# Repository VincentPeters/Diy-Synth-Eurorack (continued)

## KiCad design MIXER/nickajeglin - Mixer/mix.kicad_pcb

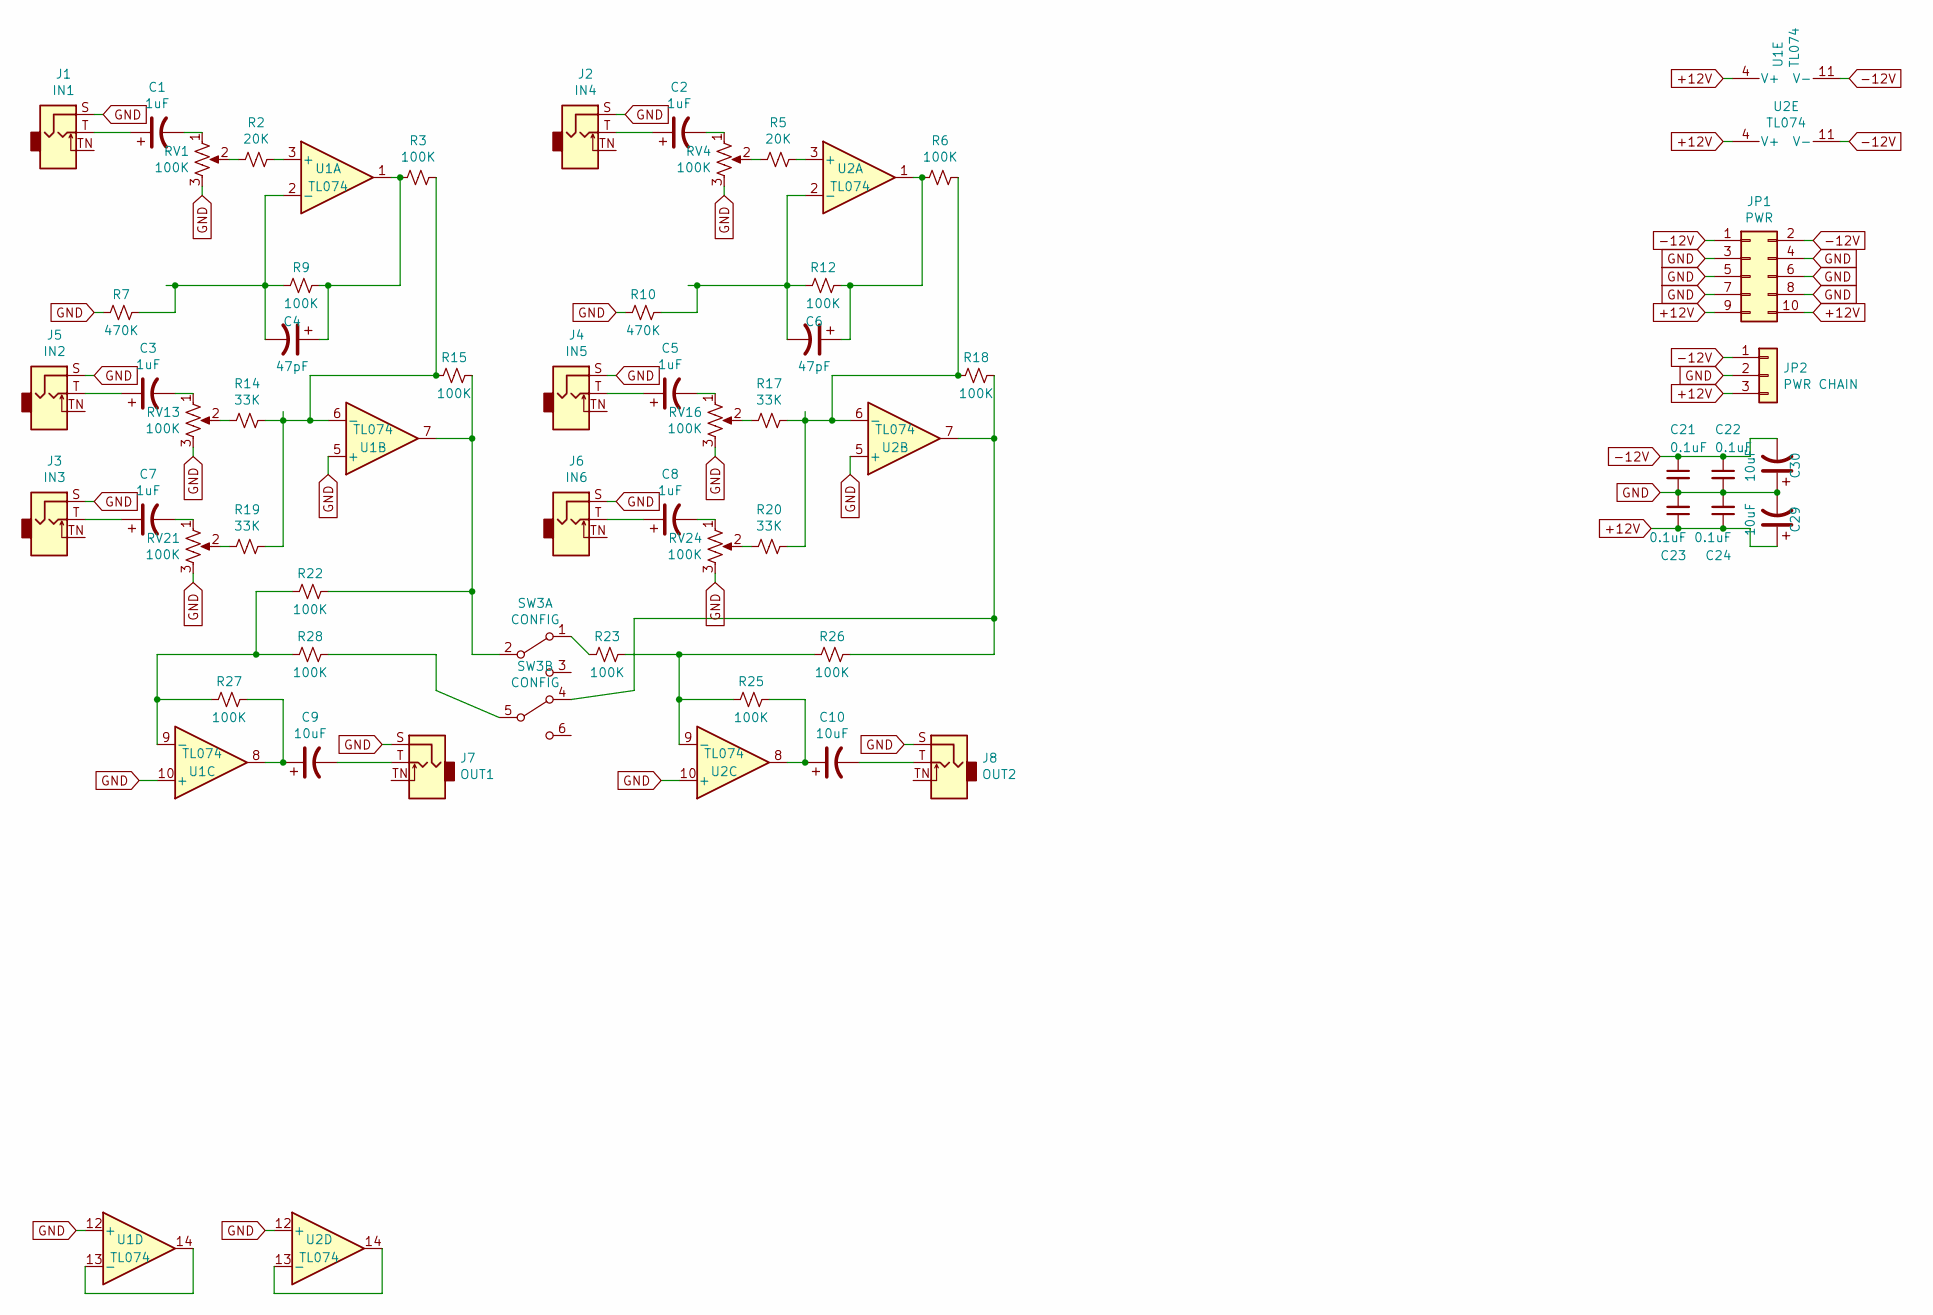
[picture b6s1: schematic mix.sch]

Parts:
C1, C2, C3, C5, C7, C8: 1uF; CP_Elec_6.3x5.4
C4, C6: 47pF; C_1206_3216Metric_Pad1.42x1.75mm_HandSolder
C9, C10, C29, C30: 10uF; CP_Elec_6.3x5.4
C21, C22, C23, C24: 0.1uF; C_1206_3216Metric_Pad1.42x1.75mm_HandSolder
J1: IN1; 3.5mm_tip_switch_thonkiconn
J2: IN4; 3.5mm_tip_switch_thonkiconn
J3: IN3; 3.5mm_tip_switch_thonkiconn
J4: IN5; 3.5mm_tip_switch_thonkiconn
J5: IN2; 3.5mm_tip_switch_thonkiconn
J6: IN6; 3.5mm_tip_switch_thonkiconn
J7: OUT1; 3.5mm_tip_switch_thonkiconn
J8: OUT2; 3.5mm_tip_switch_thonkiconn
JP1: PWR; IDC-Header_2x05_P2.54mm_Vertical
JP2: PWR CHAIN; PinHeader_1x03_P2.54mm_Vertical
R2, R5: 20K; R_1206_3216Metric_Pad1.42x1.75mm_HandSolder
R3, R6, R9, R12, R15, R18, R22, R23, R25, R26, R27, R28: 100K; R_1206_3216Metric_Pad1.42x1.75mm_HandSolder
R7, R10: 470K; R_1206_3216Metric_Pad1.42x1.75mm_HandSolder
R14, R17, R19, R20: 33K; R_1206_3216Metric_Pad1.42x1.75mm_HandSolder
RV1, RV4, RV13, RV16, RV21, RV24: 100K; Potentiometer_Thonk_Alpha_9mm_Vertical
SW3: CONFIG; toggle_switch_mini_DPDT
U1, U2: TL074; SOIC-14_3.9x8.7mm_P1.27mm

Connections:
+12V: C23.1, C24.1, C29.1, JP1.9, JP1.10, JP2.3, U1.4 (V+), U2.4 (V+)
-12V: C21.1, C22.1, C30.2, JP1.1, JP1.2, JP2.1, U1.11 (V-), U2.11 (V-)
GND: C21.2, C22.2, C23.2, C24.2, C29.2, C30.1, J1.S, J2.S, J3.S, J4.S, J5.S, J6.S, J7.S, J8.S, JP1.3, JP1.4, JP1.5, JP1.6, JP1.7, JP1.8, JP2.2, R7.2, R10.2, RV1.3, RV4.3, RV13.3, RV16.3, RV21.3, RV24.3, U1.5 (+), U1.10 (+), U1.12 (+), U2.5 (+), U2.10 (+), U2.12 (+)
unnamed: C1.1, J1.T
unnamed: C1.2, RV1.1
unnamed: C2.1, J2.T
unnamed: C2.2, RV4.1
unnamed: C3.1, J5.T
unnamed: C3.2, RV13.1
unnamed: C4.1, R3.2, R9.1, U1.1
unnamed: C5.1, J4.T
unnamed: C5.2, RV16.1
unnamed: C6.1, R6.2, R12.1, U2.1
unnamed: C7.1, J3.T
unnamed: C7.2, RV21.1
unnamed: C8.1, J6.T
unnamed: C8.2, RV24.1
unnamed: C9.1, R27.1, U1.8
unnamed: C9.2, J7.T
unnamed: C10.1, R25.1, U2.8
unnamed: C10.2, J8.T
unnamed: R2.1, U1.3 (+)
unnamed: R2.2, RV1.2
unnamed: R5.1, U2.3 (+)
unnamed: R5.2, RV4.2
unnamed: R3.1, R14.1, R15.2, R19.1, U1.6 (-)
unnamed: R14.2, RV13.2
unnamed: R15.1, R22.1, SW3.2 (B), U1.7
unnamed: R6.1, R17.1, R18.2, R20.1, U2.6 (-)
unnamed: R17.2, RV16.2
unnamed: R18.1, R26.1, SW3.4 (A), U2.7
unnamed: R19.2, RV21.2
unnamed: R20.2, RV24.2
unnamed: R22.2, R27.2, R28.2, U1.9 (-)
unnamed: R23.1, R25.2, R26.2, U2.9 (-)
unnamed: R23.2, SW3.1 (A)
unnamed: R28.1, SW3.5 (B)
unnamed: U1.13 (-), U1.14
unnamed: U2.13 (-), U2.14

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
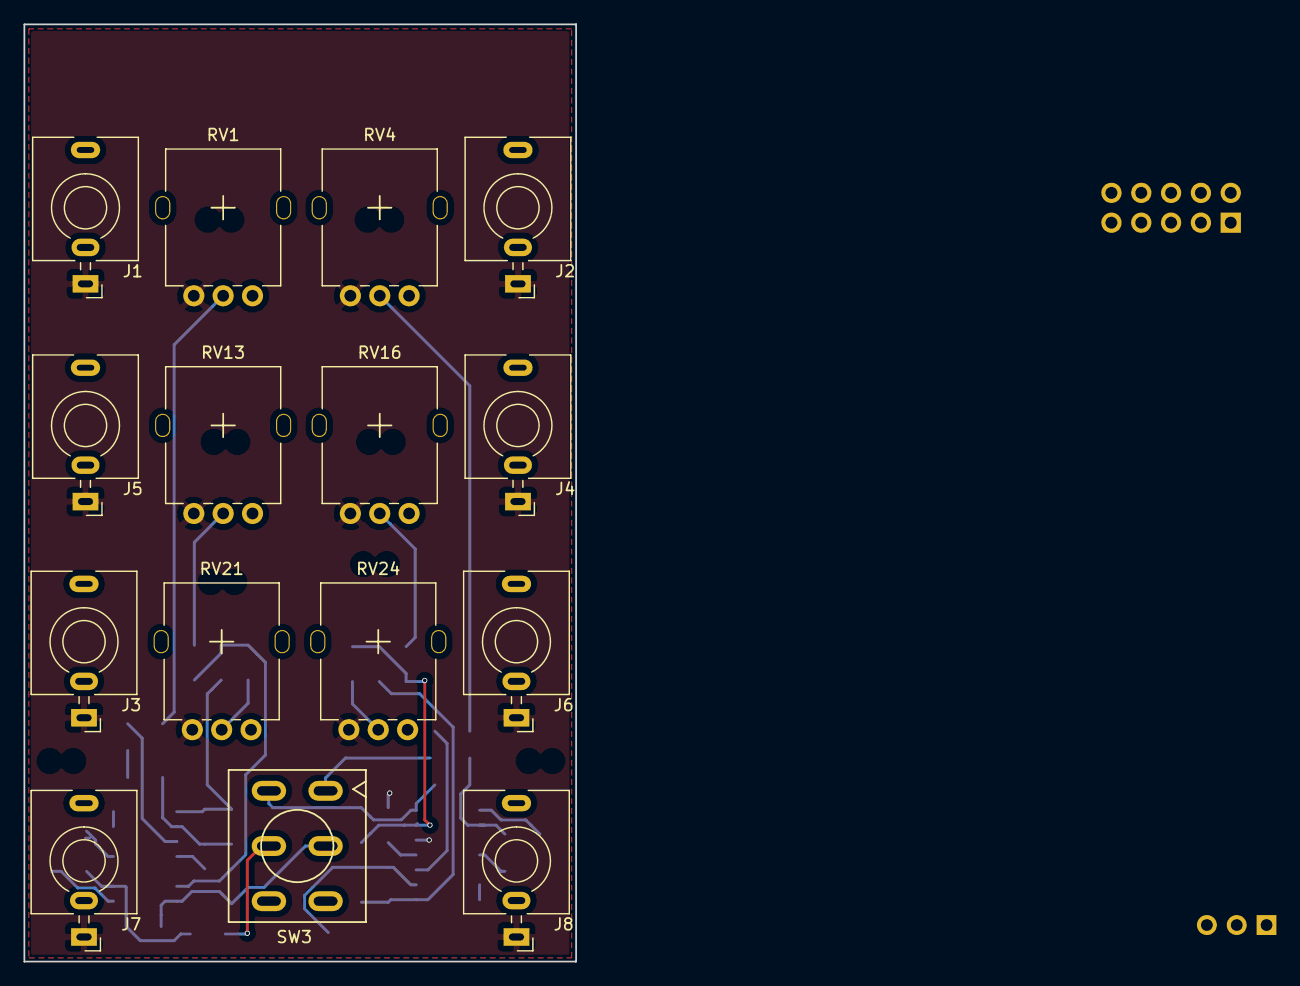
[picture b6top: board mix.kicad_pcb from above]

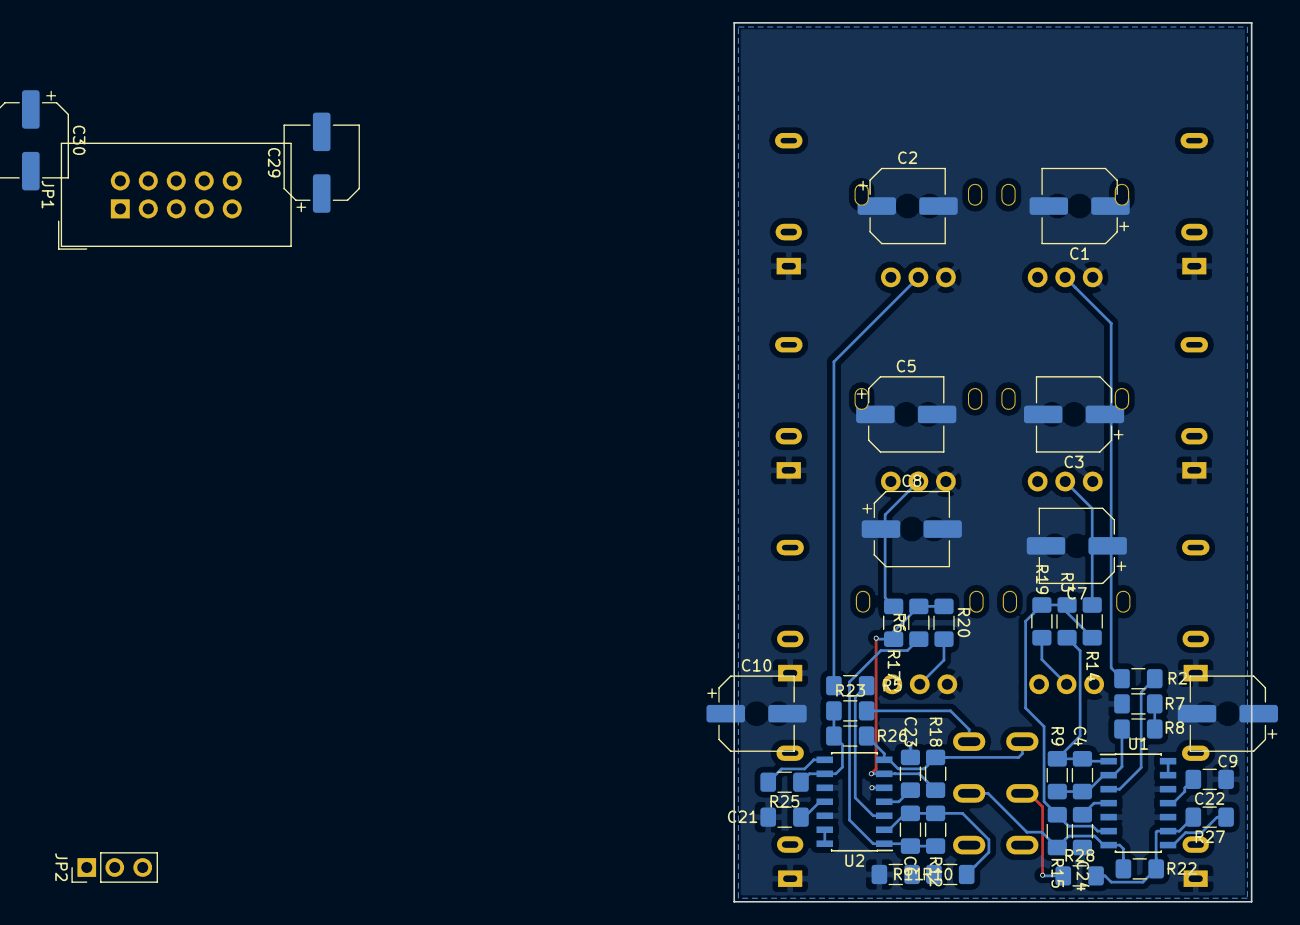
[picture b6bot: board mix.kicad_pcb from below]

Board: 2 copper layers, 47.0 x 79.8 mm, 57 parts (42 on the bottom side), 43 nets.

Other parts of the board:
R8, R11: 2K; R_1206_3216Metric_Pad1.42x1.75mm_HandSolder

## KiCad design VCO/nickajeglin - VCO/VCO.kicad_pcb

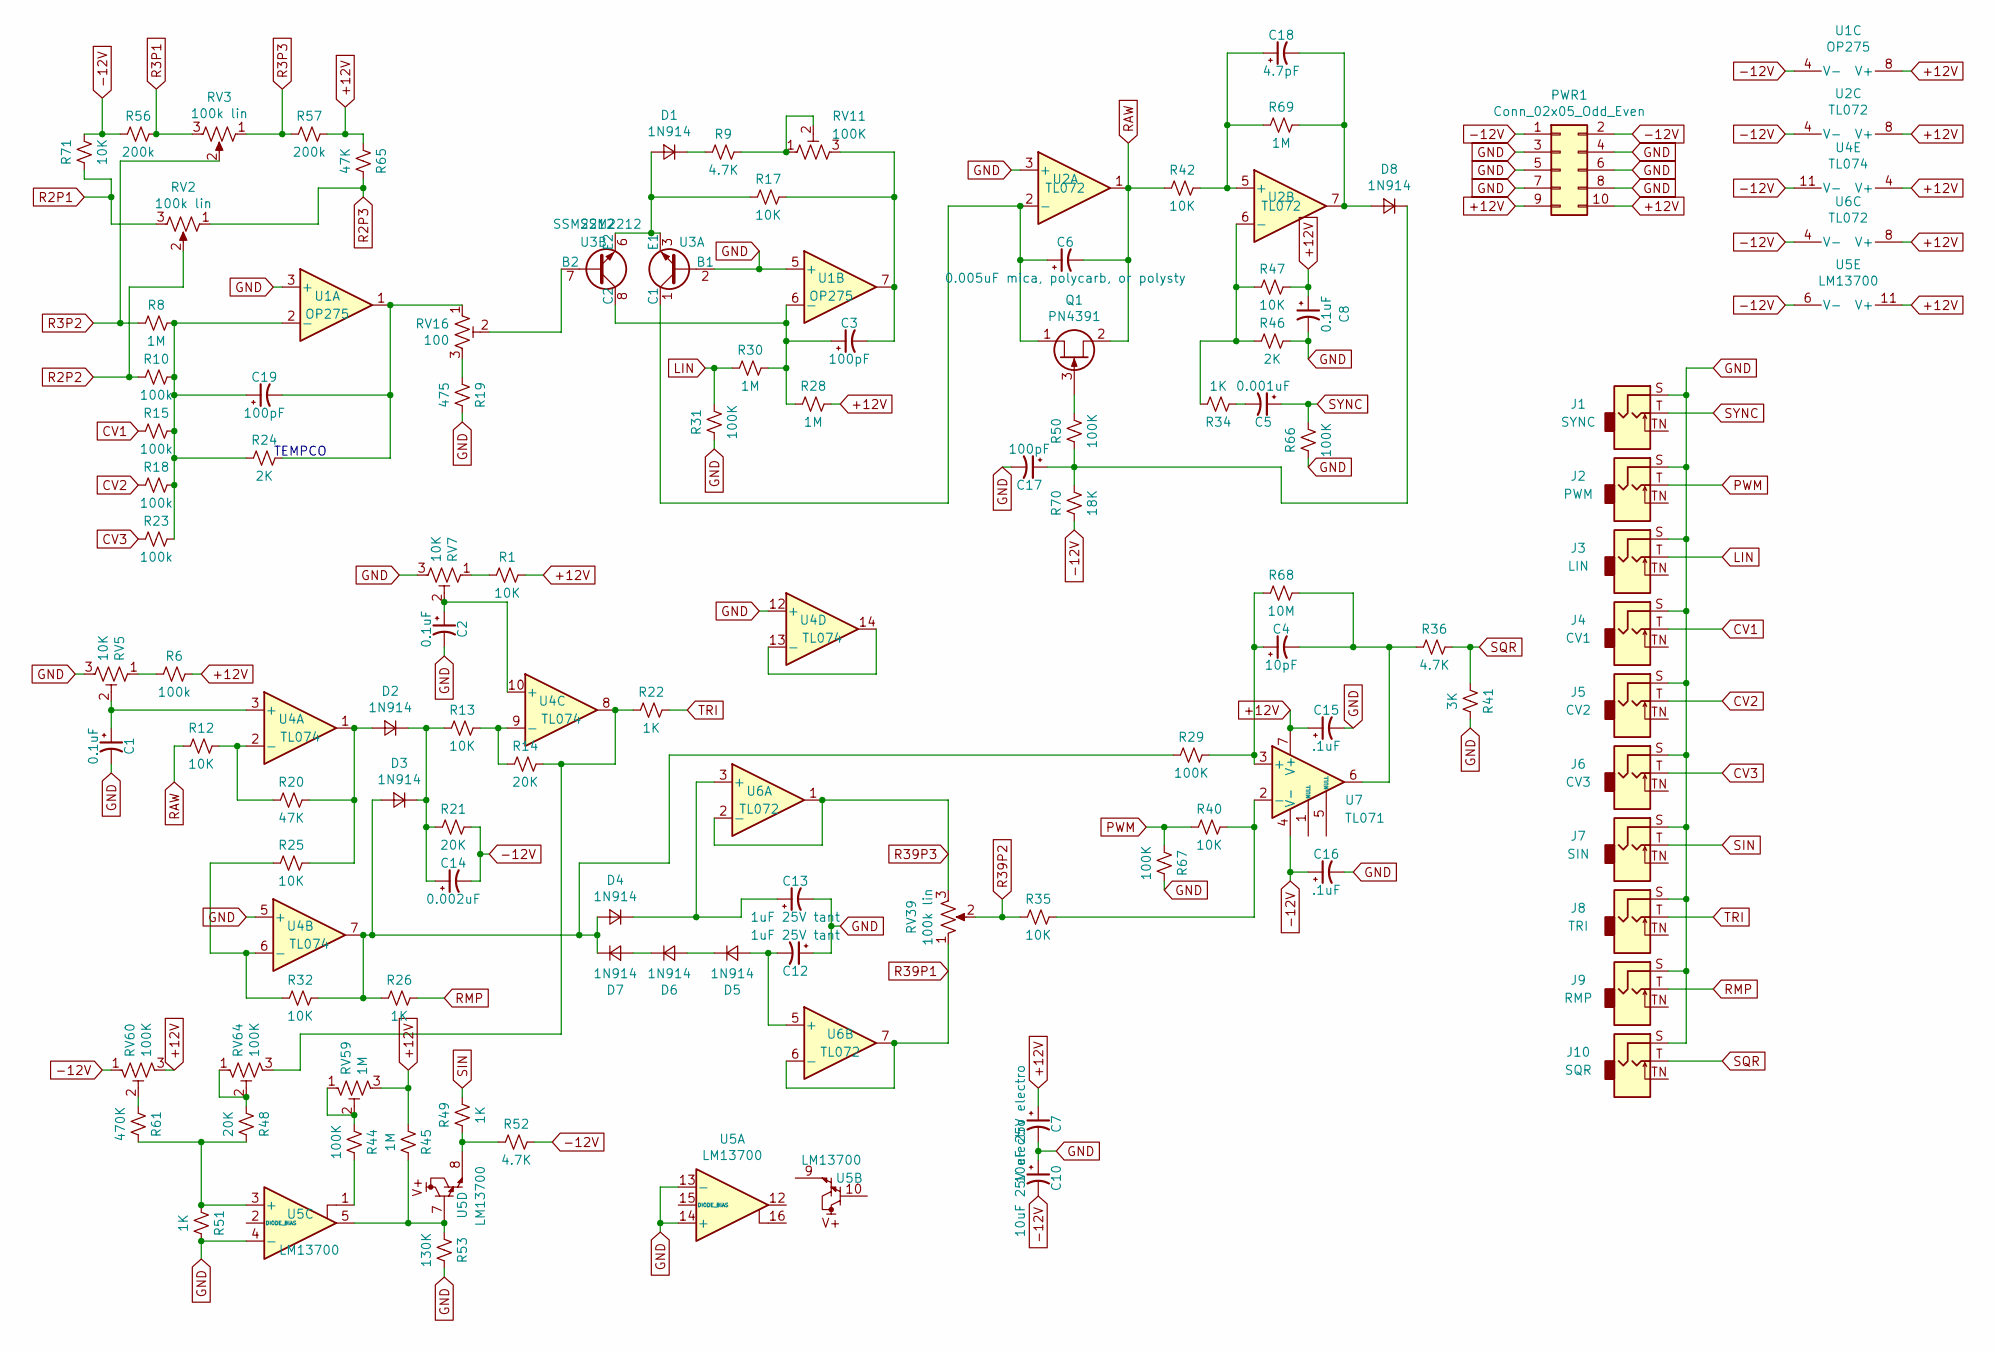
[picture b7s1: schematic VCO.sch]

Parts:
C1, C2, C8: 0.1uF; C_1206_3216Metric_Pad1.42x1.75mm_HandSolder
C3, C17, C19: 100pF; C_1206_3216Metric_Pad1.42x1.75mm_HandSolder
C4: 10pF; C_1206_3216Metric_Pad1.42x1.75mm_HandSolder
C5: 0.001uF; C_1206_3216Metric_Pad1.42x1.75mm_HandSolder
C6: 0.005uF mica, polycarb, or polysty; C_1206_3216Metric_Pad1.42x1.75mm_HandSolder
C7, C10: 10uF 25V electro; CP_Radial_D5.0mm_P2.50mm
C12, C13: 1uF 25V tant; C_1206_3216Metric_Pad1.42x1.75mm_HandSolder
C14: 0.002uF; C_1206_3216Metric_Pad1.42x1.75mm_HandSolder
C15, C16: .1uF; C_1206_3216Metric_Pad1.42x1.75mm_HandSolder
C18: 4.7pF; C_1206_3216Metric_Pad1.42x1.75mm_HandSolder
D1, D2, D3, D4, D5, D6, D7, D8: 1N914; D_1206_3216Metric_Pad1.42x1.75mm_HandSolder
J1: SYNC; 3.5mm_tip_switch_thonkiconn
J2: PWM; 3.5mm_tip_switch_thonkiconn
J3: LIN; 3.5mm_tip_switch_thonkiconn
J4: CV1; 3.5mm_tip_switch_thonkiconn
J5: CV2; 3.5mm_tip_switch_thonkiconn
J6: CV3; 3.5mm_tip_switch_thonkiconn
J7: SIN; 3.5mm_tip_switch_thonkiconn
J8: TRI; 3.5mm_tip_switch_thonkiconn
J9: RMP; 3.5mm_tip_switch_thonkiconn
J10: SQR; 3.5mm_tip_switch_thonkiconn
PWR1: Conn_02x05_Odd_Even; IDC-Header_2x05_P2.54mm_Vertical
Q1: PN4391; TO-92_Inline
R1, R12, R13, R17, R25, R32, R35, R40, R42, R47, R71: 10K; R_1206_3216Metric_Pad1.42x1.75mm_HandSolder
R6, R10, R15, R18, R23: 100k; R_1206_3216Metric_Pad1.42x1.75mm_HandSolder
R8, R28, R30, R45, R69: 1M; R_1206_3216Metric_Pad1.42x1.75mm_HandSolder
R9, R36, R52: 4.7K; R_1206_3216Metric_Pad1.42x1.75mm_HandSolder
R14, R21, R48: 20K; R_1206_3216Metric_Pad1.42x1.75mm_HandSolder
R19: 475; R_1206_3216Metric_Pad1.42x1.75mm_HandSolder
R20, R65: 47K; R_1206_3216Metric_Pad1.42x1.75mm_HandSolder
R22, R26, R34, R49, R51: 1K; R_1206_3216Metric_Pad1.42x1.75mm_HandSolder
R24, R46: 2K; R_1206_3216Metric_Pad1.42x1.75mm_HandSolder
R29, R31, R44, R50, R66, R67: 100K; R_1206_3216Metric_Pad1.42x1.75mm_HandSolder
R41: 3K; R_1206_3216Metric_Pad1.42x1.75mm_HandSolder
R53: 130K; R_1206_3216Metric_Pad1.42x1.75mm_HandSolder
R56, R57: 200k; R_1206_3216Metric_Pad1.42x1.75mm_HandSolder
R61: 470K; R_1206_3216Metric_Pad1.42x1.75mm_HandSolder
R68: 10M; R_1206_3216Metric_Pad1.42x1.75mm_HandSolder
R70: 18K; R_1206_3216Metric_Pad1.42x1.75mm_HandSolder
RV2, RV3, RV39: 100k lin; Potentiometer_Alps_RK09K_Single_Vertical
RV5, RV7: 10K; Potentiometer_Bourns_3296W_Vertical
RV11, RV60, RV64: 100K; Potentiometer_Bourns_3296W_Vertical
RV16: 100; Potentiometer_Bourns_3296W_Vertical
RV59: 1M; Potentiometer_Bourns_3296W_Vertical
U1: OP275; SOIC-8_3.9x4.9mm_P1.27mm
U2, U6: TL072; SOIC-8_3.9x4.9mm_P1.27mm
U3: SSM2212; SOIC-8_3.9x4.9mm_P1.27mm
U4: TL074; SOIC-14_3.9x8.7mm_P1.27mm
U5: LM13700; SOIC-16_3.9x9.9mm_P1.27mm
U7: TL071; SOIC-8_3.9x4.9mm_P1.27mm

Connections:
+12V: C7.1, C8.1, C15.1, PWR1.9, PWR1.10, R1.1, R6.1, R28.1, R45.2, R47.1, R57.1, R65.2, RV59.3, RV60.3, U1.8 (V+), U2.8 (V+), U4.4 (V+), U5.11 (V+), U6.8 (V+), U7.7 (V+)
-12V: C10.2, C14.2, C16.1, PWR1.1, PWR1.2, R21.1, R52.1, R56.2, R70.2, R71.1, RV60.1, U1.4 (V-), U2.4 (V-), U4.11 (V-), U5.6 (V-), U6.4 (V-), U7.4 (V-)
CV1: J4.T, R15.2
CV2: J5.T, R18.2
CV3: J6.T, R23.2
GND: C1.2, C2.2, C7.2, C8.2, C10.1, C12.1, C13.2, C15.2, C16.2, C17.2, J1.S, J2.S, J3.S, J4.S, J5.S, J6.S, J7.S, J8.S, J9.S, J10.S, PWR1.3, PWR1.4, PWR1.5, PWR1.6, PWR1.7, PWR1.8, R19.1, R31.2, R41.1, R46.1, R51.1, R53.1, R66.2, R67.1, RV5.3, RV7.3, U1.3 (+), U1.5 (+), U2.3 (+), U3.2 (B1), U4.5 (+), U4.12 (+), U5.4 (-), U5.13 (-), U5.14 (+)
LIN: J3.T, R30.2, R31.1
unnamed: C1.1, RV5.2, U4.3 (+)
unnamed: C2.1, RV7.2, U4.10 (+)
unnamed: C3.1, R28.2, R30.1, U1.6 (-), U3.8 (C2)
unnamed: C3.2, R17.1, RV11.3, U1.7
unnamed: C4.1, R29.1, R68.2, U7.3 (+)
unnamed: C4.2, R36.2, R68.1, U7.6
unnamed: C5.2, R34.2
unnamed: C6.1, Q1.1 (D), U2.2 (-), U3.1 (C1)
unnamed: C12.2, D5.2 (A), U6.5 (+)
unnamed: C13.1, D4.1 (K), U6.3 (+)
unnamed: C14.1, D2.1 (K), D3.1 (K), R13.2, R21.2
unnamed: C17.1, D8.1 (K), R50.2, R70.1
unnamed: C18.1, R42.1, R69.2, U2.5 (+)
unnamed: C18.2, D8.2 (A), R69.1, U2.7
unnamed: C19.1, R8.1, R10.1, R15.1, R18.1, R23.1, R24.2, U1.2 (-)
unnamed: C19.2, R24.1, RV16.1, U1.1
unnamed: D1.1 (K), R9.2
unnamed: D1.2 (A), R17.2, U3.3 (E1), U3.6 (E2)
unnamed: D2.2 (A), R20.1, R25.1, U4.1
unnamed: D3.2 (A), D4.2 (A), D7.1 (K), R26.2, R29.2, R32.1, U4.7
unnamed: D5.1 (K), D6.2 (A)
unnamed: D6.1 (K), D7.2 (A)
unnamed: Q1.3 (G), R50.1
unnamed: R1.2, RV7.1
unnamed: R6.2, RV5.1
unnamed: R9.1, RV11.1, RV11.2
unnamed: R12.1, R20.2, U4.2 (-)
unnamed: R13.1, R14.2, U4.9 (-)
unnamed: R14.1, R22.2, RV64.3, U4.8
unnamed: R19.2, RV16.3
unnamed: R25.2, R32.2, U4.6 (-)
unnamed: R34.1, R46.2, R47.2, U2.6 (-)
unnamed: R35.1, R40.1, U7.2 (-)
unnamed: R44.1, U5.1
unnamed: R44.2, RV59.1, RV59.2
unnamed: R45.1, R53.2, U5.5, U5.7
unnamed: R48.1, R51.2, R61.1, U5.3 (+)
unnamed: R48.2, RV64.1, RV64.2
unnamed: R49.2, R52.2, U5.8
unnamed: R61.2, RV60.2
unnamed: RV16.2, U3.7 (B2)
unnamed: U4.13 (-), U4.14
PWM: J2.T, R40.2, R67.2
R2P1: R71.2, RV2.3
R2P2: R10.2, RV2.2
R2P3: R65.1, RV2.1
R3P1: R56.1, RV3.3
R3P2: R8.2, RV3.2
R3P3: R57.2, RV3.1
R39P1: RV39.1, U6.6 (-), U6.7
R39P2: R35.2, RV39.2
R39P3: RV39.3, U6.1, U6.2 (-)
RAW: C6.2, Q1.2 (S), R12.2, R42.2, U2.1
RMP: J9.T, R26.1
SIN: J7.T, R49.1
SQR: J10.T, R36.1, R41.2
SYNC: C5.1, J1.T, R66.1
TRI: J8.T, R22.1

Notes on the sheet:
TEMPCO

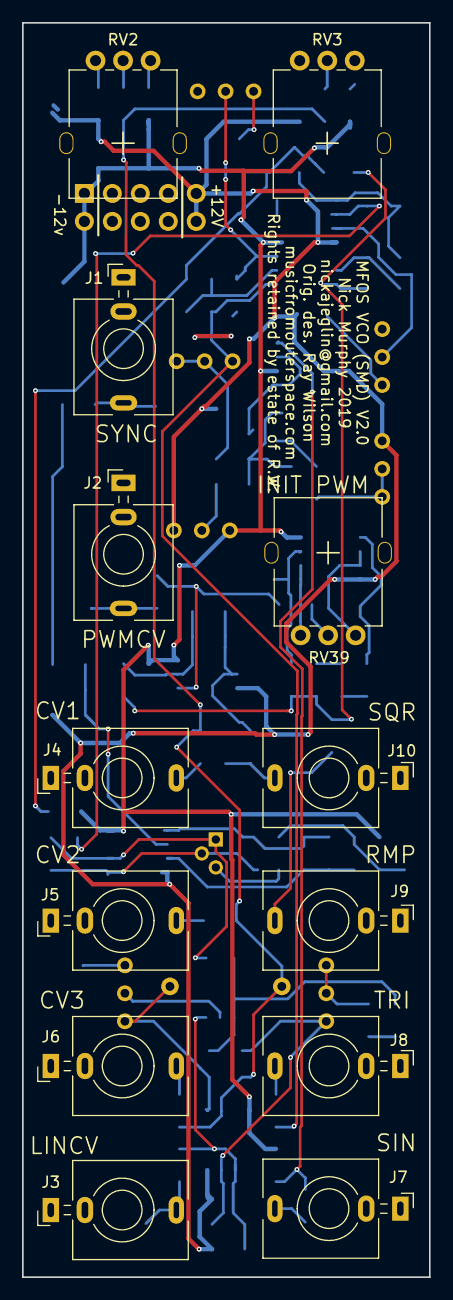
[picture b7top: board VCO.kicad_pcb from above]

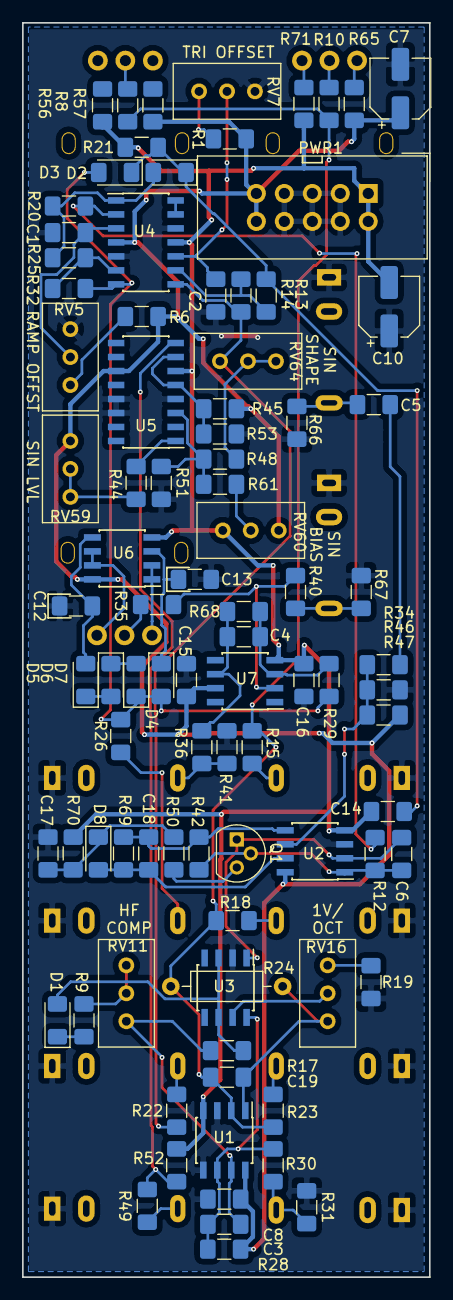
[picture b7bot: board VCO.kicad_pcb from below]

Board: 2 copper layers, 37.0 x 113.9 mm, 104 parts (91 on the bottom side), 65 nets.

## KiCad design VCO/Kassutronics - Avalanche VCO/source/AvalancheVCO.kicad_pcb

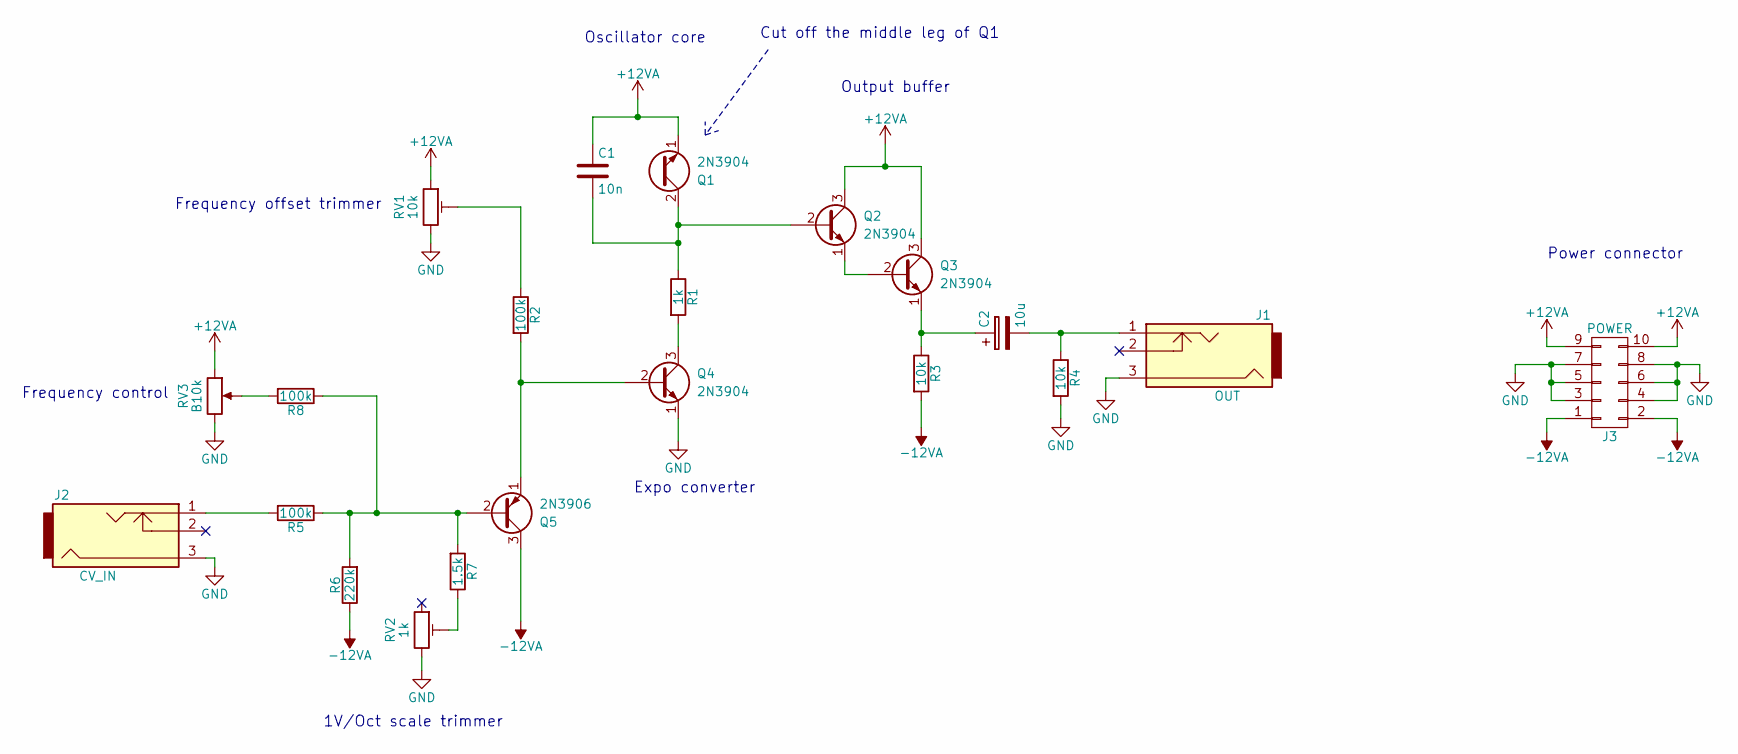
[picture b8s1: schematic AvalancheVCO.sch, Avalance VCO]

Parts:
C1: 10n; C_Rect_L7.2mm_W2.5mm_P5.00mm_FKS2_FKP2_MKS2_MKP2
C2: 10u; CP_Radial_D6.3mm_P2.50mm
J1: OUT; Thonkiconn
J2: CV_IN; Thonkiconn
J3: POWER; Pin_Header_Angled_2x05_Pitch2.54mm
Q1: 2N3904; TO-92-2pin_Inline_Wide
Q2, Q3, Q4: 2N3904; TO-92_Inline_Wide
Q5: 2N3906; TO-92_Inline_Wide
R1: 1k; R_Axial_DIN0204_L3.6mm_D1.6mm_P7.62mm_Horizontal
R2: 100k; R_Axial_DIN0204_L3.6mm_D1.6mm_P2.54mm_Vertical
R3: 10k; R_Axial_DIN0207_L6.3mm_D2.5mm_P15.24mm_Horizontal
R4: 10k; R_Axial_DIN0204_L3.6mm_D1.6mm_P7.62mm_Horizontal
R5, R8: 100k; R_Axial_DIN0204_L3.6mm_D1.6mm_P7.62mm_Horizontal
R6: 220k; R_Axial_DIN0204_L3.6mm_D1.6mm_P2.54mm_Vertical
R7: 1.5k; R_Axial_DIN0204_L3.6mm_D1.6mm_P5.08mm_Horizontal
RV1: 10k; Potentiometer_Trimmer_Bourns_3296X
RV2: 1k; Potentiometer_Trimmer_Bourns_3296X
RV3: B10k; Potentiometer_Alps_RK09K_Horizontal_ProtoBoard_Kassu

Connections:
+12VA: C1.1, J3.9, J3.10, Q1.1 (E), Q2.3 (C), Q3.3 (C), RV1.1, RV3.1
-12VA: J3.1, J3.2, Q5.3 (C), R3.2, R6.1
GND: J1.3, J2.3, J3.3, J3.4, J3.5, J3.6, J3.7, J3.8, Q4.1 (E), R4.2, RV1.3, RV2.3, RV3.3
unnamed: C1.2, Q1.2 (C), Q2.2 (B), R1.1
unnamed: C2.1, Q3.1 (E), R3.1
unnamed: C2.2, J1.1, R4.1
unnamed: J2.1, R5.2
unnamed: Q2.1 (E), Q3.2 (B)
unnamed: Q4.2 (B), Q5.1 (E), R2.2
unnamed: Q4.3 (C), R1.2
unnamed: Q5.2 (B), R5.1, R6.2, R7.2, R8.1
unnamed: R2.1, RV1.2
unnamed: R7.1, RV2.2
unnamed: R8.2, RV3.2

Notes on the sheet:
Frequency control
1V/Oct scale trimmer
Frequency offset trimmer
Oscillator core
Expo converter
Output buffer
Cut off the middle leg of Q1
Power connector

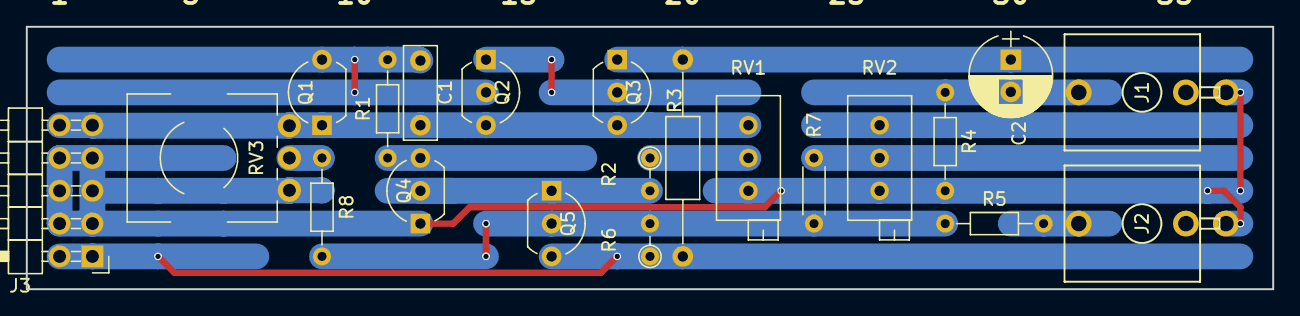
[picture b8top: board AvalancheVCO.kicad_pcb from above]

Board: 2 copper layers, 96.5 x 20.3 mm, 21 parts (0 on the bottom side), 14 nets.

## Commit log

2020-08-05 init
2020-08-05 added LMNC modules
2020-08-05 rename folder
2020-08-05 added stripboard thread
2020-08-05 added nickajeglin modules
2020-08-05 added dintree modules
2020-08-06 added some schematics, mostly drums
2020-08-09 added build pictures
2020-08-10 added simple LFO
2020-09-15 template + sequencer
2020-09-15 added readme
2020-10-01 update 1/10/2020
2020-10-01 Rename resources.md to RESOURCES.MD
2020-10-20 Order TR82
